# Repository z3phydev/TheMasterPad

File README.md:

# TheMasterPad
## What is this thing?
Well it is USB Hub that has 5 USB A ports and a USB C port... **But** it has 8 MX switches which are Programable Buttons aswell as a Rotary Encoder all of which are powered by a Seeed XIAO RP2040

## How to use
1) Assemble
2) Flash CircutPython to the XIAO (or QMK, if you do skip step 3 and 4, and if you are flashing QMK you know what you are doing anyway)
3) Download the adafruit hid lib and put it into the lib folder
4) Upload the code (which you can edit to your liking)
5) Enjoy
## Why did I make it?
I made this project because to my knowledge it hasn't been made. Even though it hasn't I still think its a good combo. It is also an intrusive thought after looking at keyboards.
## Repo Guide
- In the Folder 3D you will find the step and wrl (Kicad 3D file) files, the step is in a zip cause github said its to big and the keycaps wouldn't export so thats in ther aswell :)
- In the Kicad Folder you will find the PCB and Schematic files awell as a sub-folder containing custom footprints
- In the Firmware folder you'll find the code
- In the Production Folder you will find 3 files needed for JLC, gerbers, A BOM and Pick and Place file for assembly
- BOM.csv is the whole project cost basically. It also contains all the parts for building

## 3D Model

## PCB

## Schematic

## BOM

|Reference(s)|Qty            |Value/Description             |MFR         |MFR No.           |Unit Price GBP|Total Price GBP|Link                                                                                    |FIELD9             |FIELD10               |FIELD11        |
|------------|---------------|------------------------------|------------|------------------|--------------|---------------|----------------------------------------------------------------------------------------|-------------------|----------------------|---------------|
|~           |5 (2 assebeled)|PCB and Partial assebly       |JLCPCB      |~                 |~             |23.62          |https://jlcpcb.com/                                                                     |                   |                      |               |
|U3          |1              |Seeed XIAO RP2040 with Headers|Raspberry Pi|102010428         |4.8           |4.8            |https://thepihut.com/products/seeed-xiao-rp2040                                         |                   |                      |               |
|SW2-9       |8              |Cherry Mx Brown Swtich        |CHERRY      |MX1A-G1NW         |0.48          |4.32           |https://www.keyboardco.com/product/cherry-key-switch-module-brown-tactile-pcb-mount.asp |                   |                      |               |
|SW1         |1              |Rotary Encoder                |Bourns      |PEC11R-4325F-S0012|1.87          |1.87           |https://uk.rs-online.com/web/p/mechanical-rotary-encoders/7377767                       |                   |                      |               |
|~           |8              |Keycaps In Various Colours    |JYTECH      |JYT--1657         |0.15          |1.2            |https://www.alibaba.com/product-detail/Multi-color-XDA-Blank-Keycap-1_1601173995121.html|                   |                      |               |
|J2-6        |5              |USB A Port                    |Molex       |67643-2911        |1.78          |8.87           |https://uk.rs-online.com/web/p/usb-connectors/9048200                                   |                   |                      |               |
|            |               |                              |            |                  |              |               |                                                                                        |                   |                      |               |
|            |               |                              |            |                  |              |               |                                                                                        |                   |Total Price USD approx|Total Price GBP|
|            |               |                              |            |                  |              |               |                                                                                        |Items              |60.18                 |44.84          |
|            |               |                              |            |                  |              |               |                                                                                        |Shipping (and fees)|31.05                 |23.14          |
|            |               |                              |            |                  |              |               |                                                                                        |Final              |91.2                  |67.98          |

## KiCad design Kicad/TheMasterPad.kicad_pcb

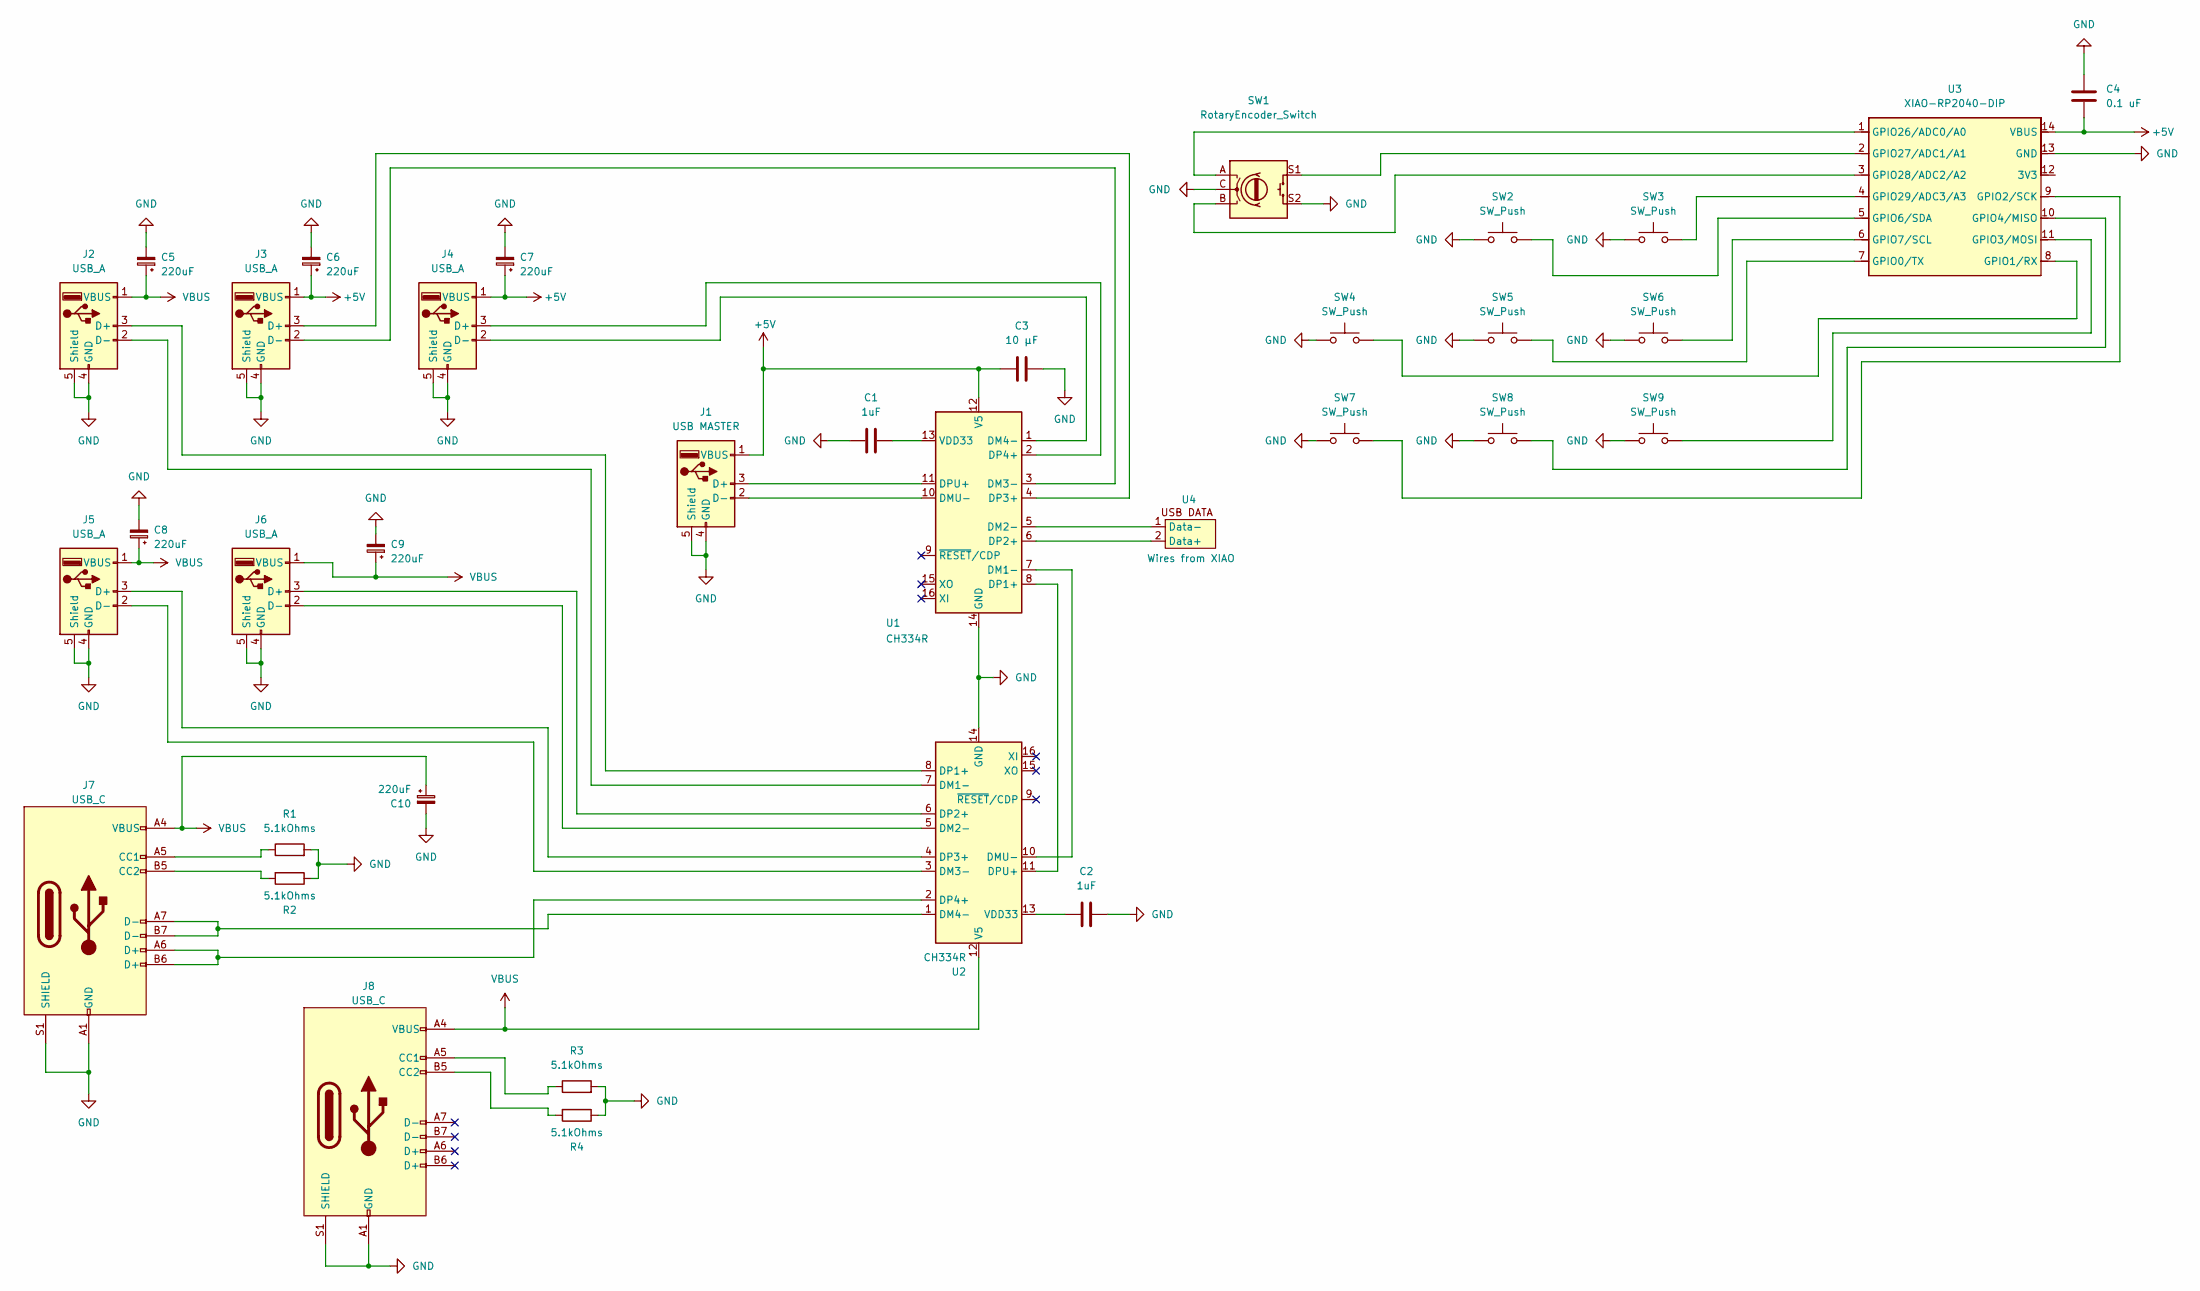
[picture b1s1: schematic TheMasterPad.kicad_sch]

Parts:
C1, C2: 1uF; C_0603_1608Metric
C3: 10 µF; C_0603_1608Metric
C4: 0.1 uF; C_0603_1608Metric
C5, C6, C7, C8, C9, C10: 220uF; C_Radial_D6.3mm_H7.0mm_P2.50mm
J1: USB MASTER; 4pinhole
J2, J3, J4, J5, J6: USB_A; USB_A_Molex_67643_Horizontal
J7, J8: USB_C; USB_C_Receptacle_Molex_105450-0101
R1, R2, R3, R4: 5.1kOhms; R_0805_2012Metric
SW1: RotaryEncoder_Switch; RotaryEncoder_Alps_EC12E-Switch_Vertical_H20mm_CircularMoun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
SW2, SW3, SW4, SW5, SW6, SW7, SW8, SW9: SW_Push; SW_Cherry_MX_1.00u_PCB
U1, U2: CH334R; QSOP-16_3.9x4.9mm_P0.635mm
U3: XIAO-RP2040-DIP
U4: Wires from XIAO; 2pinhole

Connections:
+5V: C3.1, C4.1, C6.1, C7.1, J1.1 (VBUS), J3.1 (VBUS), J4.1 (VBUS), U1.12 (V5), U3.14 (VBUS)
GND: C1.2, C2.1, C3.2, C4.2, C5.2, C6.2, C7.2, C8.2, C9.2, C10.2, J1.4 (GND), J1.5 (Shield), J2.4 (GND), J2.5 (Shield), J3.4 (GND), J3.5 (Shield), J4.4 (GND), J4.5 (Shield), J5.4 (GND), J5.5 (Shield), J6.4 (GND), J6.5 (Shield), J7.A1 (GND), J7.A12 (GND), J7.B1 (GND), J7.B12 (GND), J7.S1 (SHIELD), J8.A1 (GND), J8.A12 (GND), J8.B1 (GND), J8.B12 (GND), J8.S1 (SHIELD), R1.2, R2.1, R3.2, R4.1, SW1.C, SW1.S2, SW2.1, SW3.1, SW4.1, SW5.1, SW6.1, SW7.1, SW8.1, SW9.1, U1.14 (GND), U2.14 (GND), U3.13 (GND)
unnamed: J1.3 (D+), U1.11 (DPU+)
unnamed: J1.2 (D-), U1.10 (DMU-)
unnamed: J2.3 (D+), U2.8 (DP1+)
unnamed: J2.2 (D-), U2.7 (DM1-)
unnamed: J3.3 (D+), U1.4 (DP3+)
unnamed: J3.2 (D-), U1.3 (DM3-)
unnamed: J4.3 (D+), U1.2 (DP4+)
unnamed: J4.2 (D-), U1.1 (DM4-)
unnamed: J5.3 (D+), U2.4 (DP3+)
unnamed: J5.2 (D-), U2.3 (DM3-)
unnamed: J6.3 (D+), U2.6 (DP2+)
unnamed: J6.2 (D-), U2.5 (DM2-)
unnamed: J7.A5 (CC1), R1.1
unnamed: J7.B5 (CC2), R2.2
unnamed: J8.A5 (CC1), R3.1
unnamed: J8.B5 (CC2), R4.2
unnamed: U1.7 (DM1-), U2.10 (DMU-)
unnamed: U1.5 (DM2-), U4.1 (Data-)
unnamed: U1.8 (DP1+), U2.11 (DPU+)
unnamed: U1.6 (DP2+), U4.2 (Data+)
unnamed: C1.1, U1.13 (VDD33)
unnamed: J7.A7 (D-), J7.B7 (D-), U2.1 (DM4-)
unnamed: J7.A6 (D+), J7.B6 (D+), U2.2 (DP4+)
unnamed: C2.2, U2.13 (VDD33)
unnamed: SW5.2, U3.7 (GPIO0/TX)
unnamed: SW4.2, U3.8 (GPIO1/RX)
unnamed: SW7.2, U3.9 (GPIO2/SCK)
unnamed: SW9.2, U3.11 (GPIO3/MOSI)
unnamed: SW8.2, U3.10 (GPIO4/MISO)
unnamed: SW2.2, U3.5 (GPIO6/SDA)
unnamed: SW6.2, U3.6 (GPIO7/SCL)
unnamed: SW1.A, U3.1 (GPIO26/ADC0/A0)
unnamed: SW1.S1, U3.2 (GPIO27/ADC1/A1)
unnamed: SW1.B, U3.3 (GPIO28/ADC2/A2)
unnamed: SW3.2, U3.4 (GPIO29/ADC3/A3)
VBUS: C5.1, C8.1, C9.1, C10.1, J2.1 (VBUS), J5.1 (VBUS), J6.1 (VBUS), J7.A4 (VBUS), J7.A9 (VBUS), J7.B4 (VBUS), J7.B9 (VBUS), J8.A4 (VBUS), J8.A9 (VBUS), J8.B4 (VBUS), J8.B9 (VBUS), U2.12 (V5)

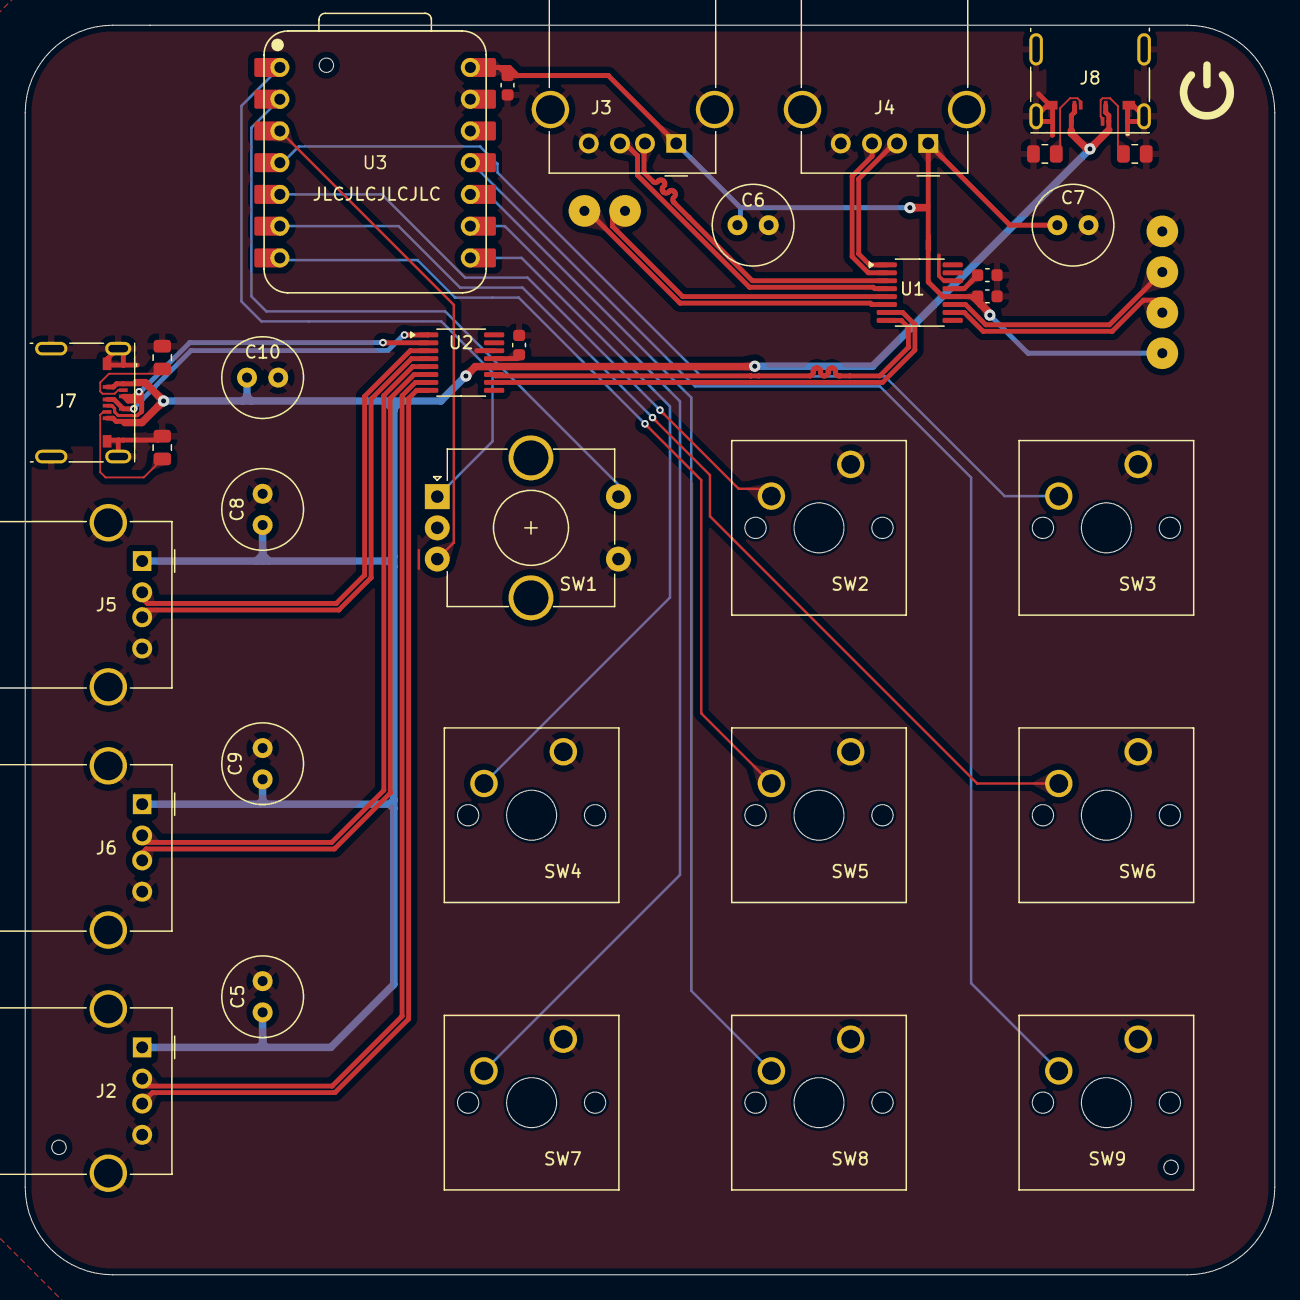
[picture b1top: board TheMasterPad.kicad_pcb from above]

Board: 2 copper layers, 100.0 x 100.0 mm, 35 parts (0 on the bottom side), 38 nets.

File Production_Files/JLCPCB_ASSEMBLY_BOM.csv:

Comment,Designator,Footprint,JLCPCB Part
CH334R,"U1, U2",QSOP-16_3.9x4.9mm_P0.635mm,C4154405
USB C Port,"J7, J8",USB_C_Receptacle_Molex_105450-0101,C134092
100nF Cap,C4,603,C14663
1uF Cap,"C1, C2",603,C15849
10uF Cap,C3,603,C19702
5.1kOhm Resistor,"R1, R2, R3, R4",805,C27834
220uF Cap,"C5, C6, C7, C8, C9, C10",D6.3xL8mm,C94440

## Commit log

2026-02-22 Created README.md
2026-02-24 Create Placeholder
2026-02-24 Expand README with project details and images
    Added detailed project description, usage instructions, and images.
2026-02-24 Add initial code file
2026-02-24 Rename Code to Code.py
2026-02-24 Add repository guide to README
    Added a repository guide section with details on files.
2026-02-24 Add schematic section to README
2026-02-24 Update README to clarify 3D folder contents
    Clarified the contents of the 3D folder in the README.
2026-02-24 Fix typo in README.md
    Corrected spelling of 'liking' in usage instructions.
2026-02-24 Update usage instructions in README.md
    Reordered the steps in the usage section for clarity.
2026-02-24 Add BOM section with components and pricing
    Added detailed BOM with components, quantities, and links.
2026-02-24 Revise usage steps in README for clarity
    Updated usage instructions for flashing and uploading code.
2026-02-24 Implement rotary encoder and macro buttons functionality
2026-02-25 Create Placehodler
2026-02-25 Update README
    Added a sub-folder note for custom footprints in Kicad.
2026-02-25 Implement rotary encoder and macro buttons for control
2026-02-25 Create Production_Files
2026-02-25 Clarify folder contents and assembly instructions
    Updated README to clarify folder contents and assembly files.
2026-03-07 Change microcontroller from Pi Pico to Seeed XIAO RP2040
    Updated the microcontroller reference from Pi Pico to Seeed XIAO RP2040.
2026-03-10 Update JLCPCB assembly BOM with new component
    Added missing component C3 to the assembly BOM.
2026-03-10 Revise BOM with updated components and prices
    Updated BOM section with new components and pricing.
2026-03-10 Remove duplicate shipping and final price entries
2026-03-10 Correct device name and update images in README
    Updated instructions to reflect the correct device name and added new images for PCB and schematic.
2026-03-10 Add images to README for 3D model and PCB
    Added images for 3D model and PCB sections.
2026-03-11 Remove duplicate entries in TheMasterPad-pos.csv
2026-03-11 Update images and BOM table in README
2026-03-11 Add BOM table with components and pricing details
